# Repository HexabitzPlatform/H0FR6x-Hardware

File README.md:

# H0FR60-Hardware
Hexabitz AC Solid State Relay Module Hardware Design

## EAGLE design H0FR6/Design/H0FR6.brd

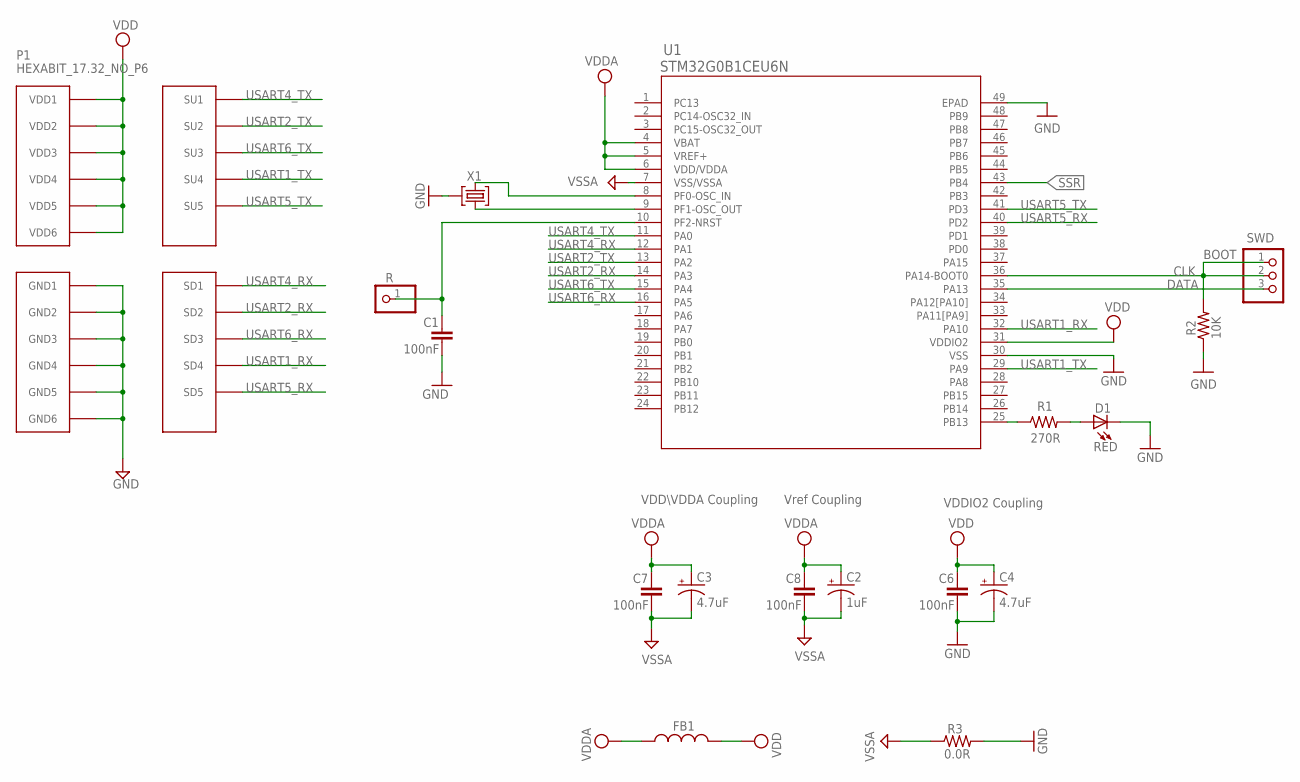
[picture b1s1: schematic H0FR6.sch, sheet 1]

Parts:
C1, C6, C7, C8: 100nF; C-0603
C2: 1uF; C-0805-POL
C3, C4: 4.7uF; C-0805-POL
D1: RED; VLMS1300-GS08; MPN VLMS1300-GS08
FB1: FB-0603
P1: HEXABIT_17.32_NO_P6
R: R; 1X01
R1: 270R; R-0603
R2: 10K; R-0603
R3: 0.0R; R-0603
SWD: PINHD-1X3; 1X03
U1: STM32G0B1CEU6N; HEXABITZ_ICS_QFN_B1CEU6_STM-L
X1: XTALL_CSTCE8M00G52

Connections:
CLK: R2.2, SWD.1, SWD.2, U1.36 (PA14-BOOT0)
DATA: SWD.3, U1.35 (PA13)
GND: C1.2, C4.2 (-), C6.2, D1.C, P1.PAD_PD7 (GND1), P1.PAD_PD8 (GND2), P1.PAD_PD9 (GND3), P1.PAD_PD10 (GND4), P1.PAD_PD11 (GND5), P1.PAD_PD12 (GND6), R2.1, R3.2, U1.30 (VSS), U1.49 (EPAD), X1.P$2 (2); also elsewhere on the board
unnamed: D1.A, R1.2
unnamed: C1.1, R.1, U1.10 (PF2-NRST)
unnamed: R1.1, U1.25 (PB13)
unnamed: U1.9 (PF1-OSC_OUT), X1.P$1 (1)
unnamed: U1.8 (PF0-OSC_IN), X1.P$3 (3)
SSR: U1.43 (PB4); also elsewhere on the board
USART1_RX: P1.PAD_PD4 (SD4), U1.32 (PA10)
USART1_TX: P1.PAD_PU4 (SU4), U1.29 (PA9)
USART2_RX: P1.PAD_PD2 (SD2), U1.14 (PA3)
USART2_TX: P1.PAD_PU2 (SU2), U1.13 (PA2)
USART4_RX: P1.PAD_PD1 (SD1), U1.12 (PA1)
USART4_TX: P1.PAD_PU1 (SU1), U1.11 (PA0)
USART5_RX: P1.PAD_PD5 (SD5), U1.40 (PD2)
USART5_TX: P1.PAD_PU5 (SU5), U1.41 (PD3)
USART6_RX: P1.PAD_PD3 (SD3), U1.16 (PA5)
USART6_TX: P1.PAD_PU3 (SU3), U1.15 (PA4)
VDD: C4.1 (+), C6.1, FB1.2, P1.PAD_PU7 (VDD1), P1.PAD_PU8 (VDD2), P1.PAD_PU9 (VDD3), P1.PAD_PU10 (VDD4), P1.PAD_PU11 (VDD5), P1.PAD_PU12 (VDD6), U1.31 (VDDIO2); also elsewhere on the board
VDDA: C2.1 (+), C3.1 (+), C7.1, C8.1, FB1.1, U1.4 (VBAT), U1.5 (VREF+), U1.6 (VDD/VDDA)
VSSA: C2.2 (-), C3.2 (-), C7.2, C8.2, R3.1, U1.7 (VSS/VSSA)

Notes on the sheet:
Vref Coupling
VDDIO2 Coupling
VDD\VDDA Coupling
BOOT

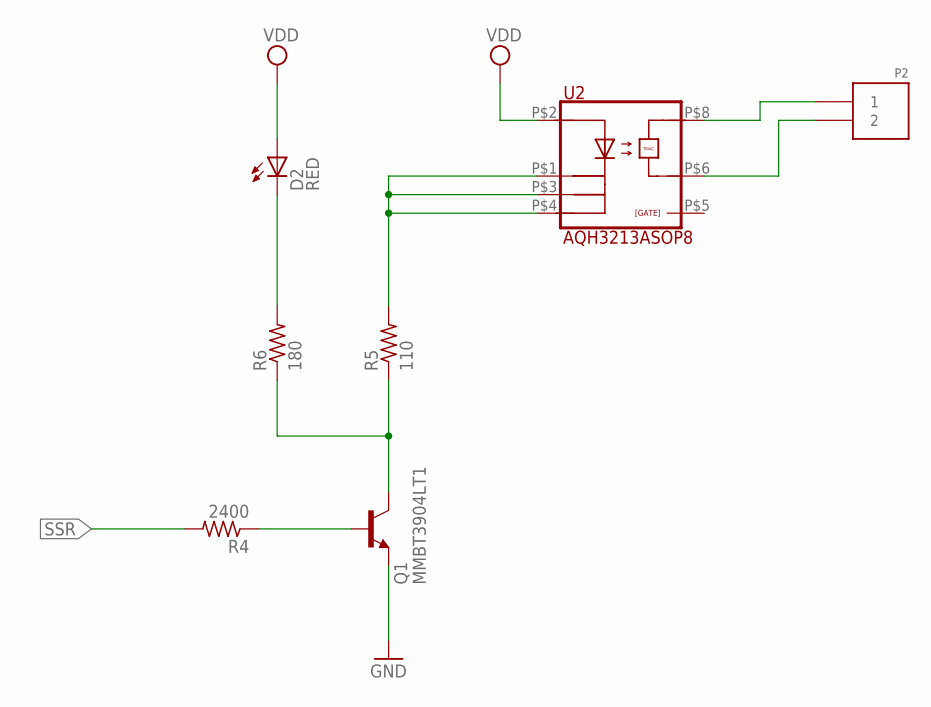
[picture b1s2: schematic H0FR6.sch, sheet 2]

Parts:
D2: RED; VLMS1300-GS08; MPN VLMY1300-GS08
P2: 1546111-2
Q1: MMBT3904LT1; VOLTAGE_RATING_DC 40.0 V; MPN MMBT3904LT1G
R4: 2400; R-0603; TOLERANCE ±5%; MPN RC0603JR-070RL
R5: 110; R-0603; TOLERANCE ±1%; MPN RC0402FR-07100RL
R6: 180; R-0603; TOLERANCE ±5%; MPN RC0402FR-07100RL
U2: AQH3213ASOP8; AQH3213A

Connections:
GND: Q1.2 (E); also elsewhere on the board
unnamed: P2.1, U2.P$8
unnamed: P2.2, U2.P$6
unnamed: D2.C, R6.2
unnamed: R5.2, U2.P$1, U2.P$3, U2.P$4
unnamed: Q1.3 (C), R5.1, R6.1
unnamed: Q1.1 (B), R4.1
SSR: R4.2; also elsewhere on the board
VDD: D2.A, U2.P$2; also elsewhere on the board

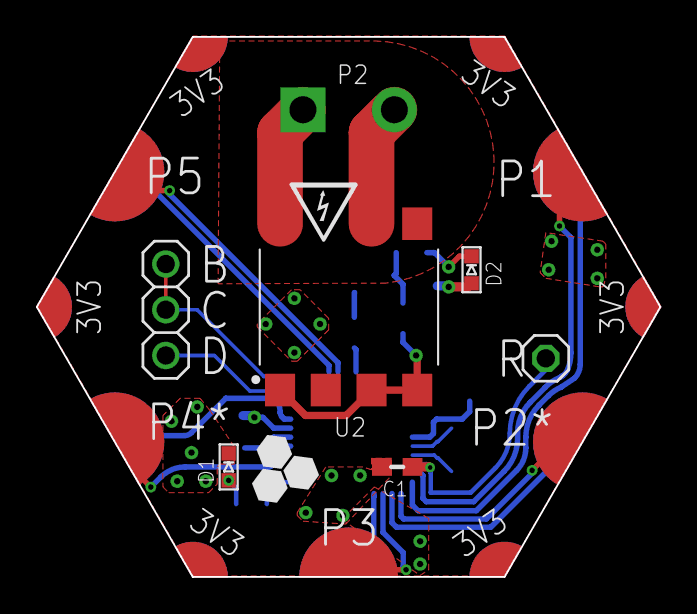
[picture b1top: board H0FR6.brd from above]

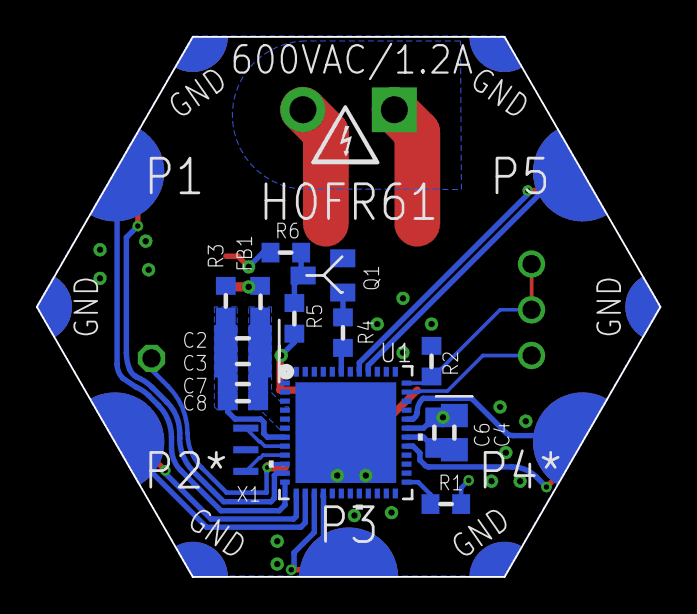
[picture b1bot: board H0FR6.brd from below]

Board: 2 copper layers, 34.6 x 30.0 mm, 24 parts (16 on the bottom side), 28 nets.

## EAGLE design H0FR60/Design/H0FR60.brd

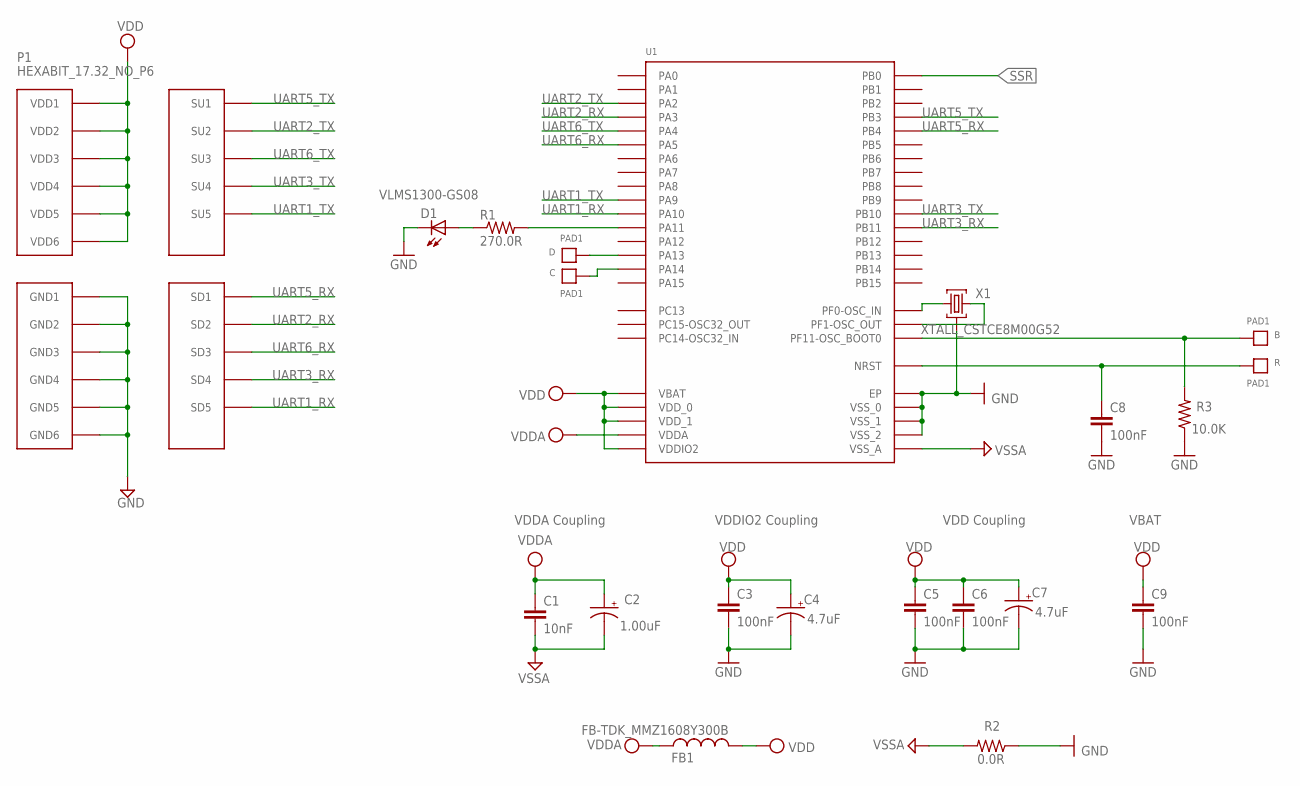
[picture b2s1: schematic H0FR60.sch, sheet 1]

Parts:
B: PAD1
C: PAD1
C1: 10nF; C-0603; TOLERANCE 10%; VOLTAGE_RATING 50V; MPN C0603C103K5RACTU
C2: 1.00uF; C-0805-POL; TOLERANCE 10%; VOLTAGE_RATING 16V; MPN CC0805KKX7R7BB105
C3, C6, C8: 100nF; C-0603; TOLERANCE 10%; VOLTAGE_RATING 10V; MPN C0603C104K8RACTU
C4, C7: 4.7uF; C-0805-POL; TOLERANCE 10%; VOLTAGE_RATING 25V; MPN GRM21BC81E475KA12L
C5: 100nF; C-0603; TOLERANCE 10%; VOLTAGE_RATING 10; MPN C0603C104K8RACTU
C9: 100nF; C-0603; TOLERANCE 10V; VOLTAGE_RATING 10%; MPN C0603C104K8RACTU
D: PAD1
D1: VLMS1300-GS08; MPN VLMS1300-GS08
FB1: FB-TDK_MMZ1608Y300B; MPN MMZ1608Y300B
P1: HEXABIT_17.32_NO_P6
R: PAD1
R1: 270.0R; R-0603; TOLERANCE 1%; MPN RC0603FR-07270RL
R2: 0.0R; R-0603; MPN RC0603JR-070RL
R3: 10.0K; R-0603; TOLERANCE 5%; MPN RC0603JR-0710KL
U1: STM32F091CBU6
X1: XTALL_CSTCE8M00G52

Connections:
B1: B.P$1, B.P$2, R3.2, U1.P$44 (PF11-OSC_BOOT0)
GND: C3.2, C4.2 (-), C5.2, C6.2, C7.2 (-), C8.2, C9.2, D1.C, P1.PAD_PD7 (GND1), P1.PAD_PD8 (GND2), P1.PAD_PD9 (GND3), P1.PAD_PD10 (GND4), P1.PAD_PD11 (GND5), P1.PAD_PD12 (GND6), R2.1, R3.1, U1.EP, U1.P$23 (VSS_0), U1.P$35 (VSS_1), U1.P$47 (VSS_2), X1.P$2 (2); also elsewhere on the board
unnamed: D.P$1, D.P$2, U1.P$34 (PA13)
unnamed: C.P$1, C.P$2, U1.P$37 (PA14)
unnamed: R1.2, U1.P$32 (PA11)
unnamed: D1.A, R1.1
unnamed: U1.P$5 (PF0-OSC_IN), X1.P$1 (1)
unnamed: U1.P$6 (PF1-OSC_OUT), X1.P$3 (3)
R1: C8.1, R.P$1, R.P$2, U1.P$7 (NRST)
SSR: U1.P$18 (PB0); also elsewhere on the board
UART1_RX: P1.PAD_PD5 (SD5), U1.P$31 (PA10)
UART1_TX: P1.PAD_PU5 (SU5), U1.P$30 (PA9)
UART2_RX: P1.PAD_PD2 (SD2), U1.P$13 (PA3)
UART2_TX: P1.PAD_PU2 (SU2), U1.P$12 (PA2)
UART3_RX: P1.PAD_PD4 (SD4), U1.P$22 (PB11)
UART3_TX: P1.PAD_PU4 (SU4), U1.P$21 (PB10)
UART5_RX: P1.PAD_PD1 (SD1), U1.P$40 (PB4)
UART5_TX: P1.PAD_PU1 (SU1), U1.P$39 (PB3)
UART6_RX: P1.PAD_PD3 (SD3), U1.P$15 (PA5)
UART6_TX: P1.PAD_PU3 (SU3), U1.P$14 (PA4)
VDD: C3.1, C4.1 (+), C5.1, C6.1, C7.1 (+), C9.1, FB1.2, P1.PAD_PU7 (VDD1), P1.PAD_PU8 (VDD2), P1.PAD_PU9 (VDD3), P1.PAD_PU10 (VDD4), P1.PAD_PU11 (VDD5), P1.PAD_PU12 (VDD6), U1.P$1 (VBAT), U1.P$24 (VDD_0), U1.P$36 (VDDIO2), U1.P$48 (VDD_1); also elsewhere on the board
VDDA: C1.1, C2.1 (+), FB1.1, U1.P$9 (VDDA)
VSSA: C1.2, C2.2 (-), R2.2, U1.P$8 (VSS_A)

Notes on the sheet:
VDDA Coupling
VDDIO2 Coupling
VDD Coupling
VBAT

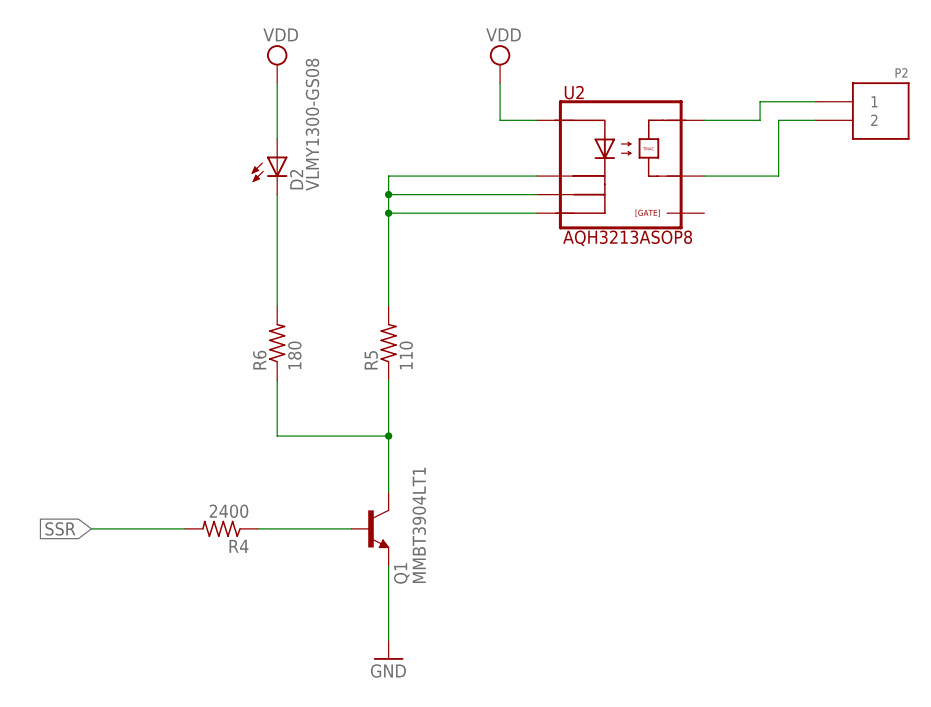
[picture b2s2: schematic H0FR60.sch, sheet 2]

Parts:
D2: VLMY1300-GS08; VLMS1300-GS08; MPN VLMY1300-GS08
P2: 1546111-2
Q1: MMBT3904LT1; VOLTAGE_RATING_DC 40.0 V; MPN MMBT3904LT1G
R4: 2400; R-0603; TOLERANCE ±5%; MPN RC0603JR-070RL
R5: 110; R-0603; TOLERANCE ±1%; MPN RC0402FR-07100RL
R6: 180; R-0603; TOLERANCE ±5%; MPN RC0402FR-07100RL
U2: AQH3213ASOP8; AQH3213A; MPN AQH3213A

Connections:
GND: Q1.2 (E); also elsewhere on the board
unnamed: P2.1, U2.P$8 (8)
unnamed: P2.2, U2.P$6 (6)
unnamed: D2.C, R6.2
unnamed: R5.2, U2.P$1 (1), U2.P$3 (3), U2.P$4 (4)
unnamed: Q1.3 (C), R5.1, R6.1
unnamed: Q1.1 (B), R4.1
SSR: R4.2; also elsewhere on the board
VDD: D2.A, U2.P$2 (2); also elsewhere on the board

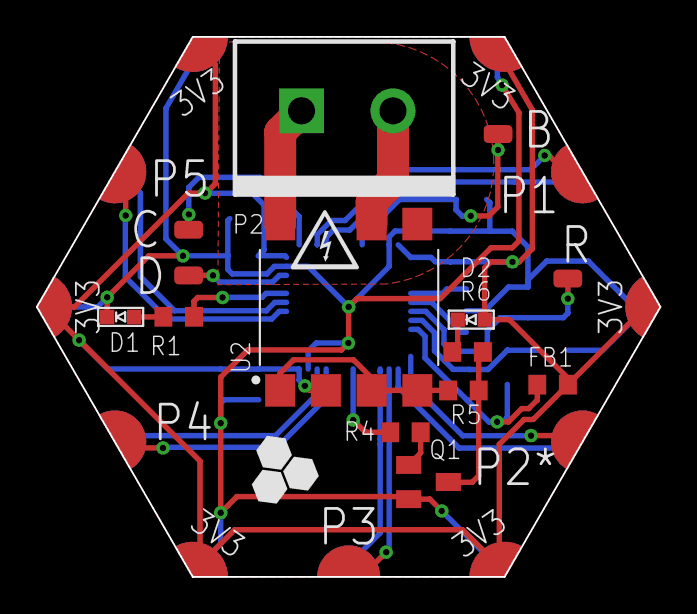
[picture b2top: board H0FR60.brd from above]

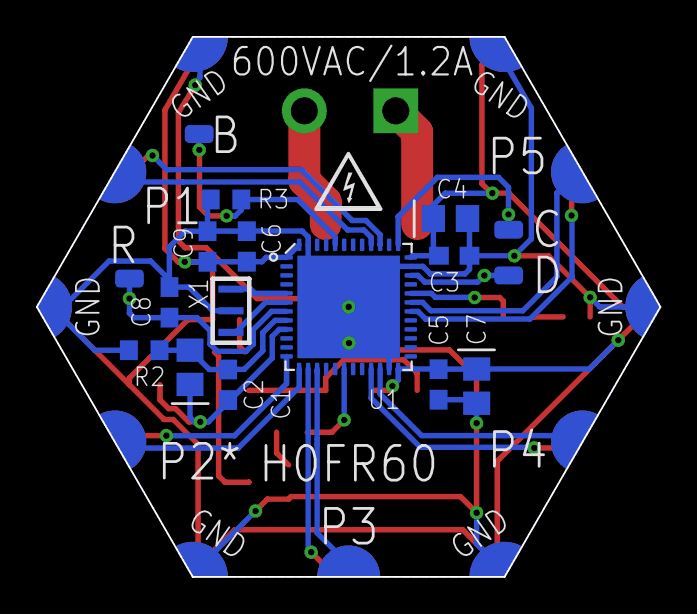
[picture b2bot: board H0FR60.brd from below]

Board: 2 copper layers, 34.6 x 30.0 mm, 28 parts (13 on the bottom side), 29 nets.

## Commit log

2019-05-23 First release rev 0
2024-02-17 -Changing the MCU to STM32G0B1CEU6N

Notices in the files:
parts and their libraries:
HEXABITZ_ICs: COPYRIGHT: Copyright (C) 2022 Ultra Librarian. All rights reserved.
